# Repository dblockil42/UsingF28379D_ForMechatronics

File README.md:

<div id="top"></div>
<!--
*** Thanks for checking out the Best-README-Template. If you have a suggestion
*** that would make this better, please fork the repo and create a pull request
*** or simply open an issue with the tag "enhancement".
*** Don't forget to give the project a star!
*** Thanks again! Now go create something AMAZING! :D
-->

<!-- PROJECT SHIELDS -->
<!--
*** I'm using markdown "reference style" links for readability.
*** Reference links are enclosed in brackets [ ] instead of parentheses ( ).
*** See the bottom of this document for the declaration of the reference variables
*** for contributors-url, forks-url, etc. This is an optional, concise syntax you may use.
*** https://www.markdownguide.org/basic-syntax/#reference-style-links
-->
[![Contributors][contributors-shield]][contributors-url]
[![Forks][forks-shield]][forks-url]
[![Stargazers][stars-shield]][stars-url]
[![Issues][issues-shield]][issues-url]
[![MIT License][license-shield]][license-url]
[![LinkedIn][linkedin-shield]][linkedin-url]

<!-- PROJECT LOGO -->
<br />
<div align="center">

  <h3 align="center">Instructing Mechatronics with the Texas Instruments TMS320F28379D</h3>

  <p align="center">
    Mechatronics, Robotics and Real-Time Control with the TI TMS320F28379D Processor
    <br />
    <a href="https://github.com/dblockil42/UsingF28379D_ForMechatronics"><strong>Explore the docs »</strong></a>
    <br />
    <br />
    <a href="https://www.youtube.com/playlist?list=PL-l3usZMjrdI7pazXXURZ83wFKBJd2WC6">View YouTube Channel</a>
    ·
    <a href="https://github.com/dblockil42/UsingF28379D_ForMechatronics/issues">Report Bug</a>
    ·
    <a href="https://github.com/dblockil42/UsingF28379D_ForMechatronics/issues">Request Feature</a>
  </p>
</div>

<!-- TABLE OF CONTENTS -->
<details>
  <summary>Table of Contents</summary>
  <ol>
    <li>
      <a href="#about-the-project">About The Project</a>
      <ul>
        <li><a href="#built-with">Built With</a></li>
      </ul>
    </li>
    <li>
      <a href="#getting-started">Getting Started</a>
      <ul>
        <li><a href="#prerequisites">Prerequisites</a></li>
        <li><a href="#installation">Installation</a></li>
      </ul>
    </li>
    <li><a href="#usage">Usage</a></li>
    <li><a href="#roadmap">Roadmap</a></li>
    <li><a href="#contributing">Contributing</a></li>
    <li><a href="#license">License</a></li>
    <li><a href="#contact">Contact</a></li>
    <li><a href="#acknowledgments">Acknowledgments</a></li>
  </ol>
</details>

<!-- ABOUT THE PROJECT -->
## About The Project
The TMS320F28379D is an incredibly powerful processor for embedded control design.

I have been teaching with the C2000 series of processors since the early 2000s with the F2407 processor and a bit later the F2808.  Currently in my lab instruction I use the F28335, F28379D and F28027 processors.

I use the F2837x processor in the classes:
- [ME461, Computer Control of Mechanical Systems](http://coecsl.ece.illinois.edu/me461),
- [SE420, Digital Control of Dynamic Systems](http://coecsl.ece.illinois.edu/se420),
- [SE423, Mechatronics](http://coecsl.ece.illinois.edu/se423).  
	
You can find these classes and all the rest of the classes that use the Grainger College of Engineering Control Systems Lab at http://coecsl.ece.illinois.edu  

I have created a YouTube channel that has parts of my SE423 and ME461 lectures describing how to use/program the TMS320F28379D processor.  Please visit [Dan Block's YouTube Channel](https://www.youtube.com/watch?v=pqUko_UUdbc&list=PL-l3usZMjrdI7pazXXURZ83wFKBJd2WC6&index=1)
	
This is a picture and link to a final project that one of the students taking ME461 created. 
[![Product Name Screen Shot][product-screenshot]](https://www.hackster.io/yixiaol2/control-segbot-with-tv-remote-98b02c)
See her additional F28379D based projects at https://www.hackster.io/yixiaol2

<p align="right">(<a href="#top">back to top</a>)</p>

### Built With

Texas Instruments C2000Ware was used to develop the given C2000 projects.  If you are interested in the SYS/BIOS (coming soon) project you will need to also install SYS/BIOS under Code Composer Studio.

* [C2000Ware 4.01](https://www.ti.com/tool/C2000WARE)
* [SYS/BIOS 6.83.00.18](https://software-dl.ti.com/dsps/dsps_public_sw/sdo_sb/targetcontent/bios/sysbios/)

<p align="right">(<a href="#top">back to top</a>)</p>

<!-- GETTING STARTED -->
## Getting Started

You will need to have installed Texas Instruments Code Composer Studio.  I am currently using version 11.2

### Prerequisites

Access to the LAUNCHXL-F28379D Development Board https://www.ti.com/tool/LAUNCHXL-F28379D.

Fabricate the Breakout board I developed for the LAUNCHXL-F28379D https://github.com/dblockil42/UsingF28379D_ForMechatronics/tree/main/EagleCAD_ME461Board.

Knowledge of C programming is very important.

### Installation

_Steps for installing:_

1. Download and install CCS 11.2  [https://www.ti.com/tool/download/CCSTUDIO](https://www.ti.com/tool/download/CCSTUDIO)
2. Download and install C2000Ware 4.01 https://www.ti.com/tool/C2000WARE  Actually not directly needed, as all source code is included in this repository, but by installing C2000Ware you will agree with Texas Instruments License for C2000Ware.  
3. Clone the repo
   ```sh
   git clone https://github.com/dblockil42/UsingF28379D_ForMechatronics.git
   ```
4. Install SYS/BIOS if you would like to use the SYS/BIOS example (coming soon)

<p align="right">(<a href="#top">back to top</a>)</p>

<!-- USAGE EXAMPLES -->
## Usage

Best to start at the YouTube channel :  Coming Soon

For more examples, please refer to the class websites [SE423 (Mechatronics](http://coecsl.ece.illinois.edu/se423) and [ME461 (Computer Control of Mechanical Systems)](http://coecsl.ece.illinois.edu/me461)

<p align="right">(<a href="#top">back to top</a>)</p>

<!-- ROADMAP -->
## Roadmap

- [ ] Add More Starter Projects for additional Peripherals
- [ ] Add SYS/BIOS Starter Project
- [ ] Continue to add videos to YouTube channel explaining the given Starter Projects in detail.

See the [open issues](https://github.com/dblockil42/UsingF28379D_ForMechatronics/issues) for a full list of proposed features (and known issues).

<p align="right">(<a href="#top">back to top</a>)</p>

<!-- CONTRIBUTING -->
## Contributing

Contributions are what make the open source community such an amazing place to learn, inspire, and create. Any contributions you make are **greatly appreciated**.

If you have a suggestion that would make this better, please fork the repo and create a pull request. You can also simply open an issue with the tag "enhancement".
Don't forget to give the project a star! Thanks again!  Please Note, that during the two college semesters I am very busy instructing my classes so I cannot promise how quick I will get to new Pull Requests.  I will do my best to get to them.  

1. Fork the Project
2. Create your Feature Branch (`git checkout -b feature/AmazingFeature`)
3. Commit your Changes (`git commit -m 'Add some AmazingFeature'`)
4. Push to the Branch (`git push origin feature/AmazingFeature`)
5. Open a Pull Request

<p align="right">(<a href="#top">back to top</a>)</p>

<!-- LICENSE -->
## License

Distributed under the  MIT License. See `LICENSE.txt` for more information.

<p align="right">(<a href="#top">back to top</a>)</p>

<!-- CONTACT -->
## Contact

Dan Block -  dblockil42@gmail.com

Project Link: [https://github.com/dblockil42/UsingF28379D_ForMechatronics](https://github.com/dblockil42/UsingF28379D_ForMechatronics)

<p align="right">(<a href="#top">back to top</a>)</p>

<!-- ACKNOWLEDGMENTS -->
## Acknowledgments

Many of my students with their questions helped me put this together!  

* [Template this Readme Started From](https://github.com/othneildrew/Best-README-Template#top)
* [Choose an Open Source License](https://choosealicense.com)
* [GitHub Emoji Cheat Sheet](https://www.webpagefx.com/tools/emoji-cheat-sheet)
* [Malven's Flexbox Cheatsheet](https://flexbox.malven.co/)
* [Malven's Grid Cheatsheet](https://grid.malven.co/)
* [Img Shields](https://shields.io)
* [GitHub Pages](https://pages.github.com)
* [Font Awesome](https://fontawesome.com)
* [React Icons](https://react-icons.github.io/react-icons/search)

<p align="right">(<a href="#top">back to top</a>)</p>

<!-- MARKDOWN LINKS & IMAGES -->
<!-- https://www.markdownguide.org/basic-syntax/#reference-style-links -->
[contributors-shield]: https://img.shields.io/github/contributors/dblockil42/UsingF28379D_ForMechatronics.svg?style=for-the-badge
[contributors-url]: https://github.com/dblockil42/UsingF28379D_ForMechatronics/graphs/contributors
[forks-shield]: https://img.shields.io/github/forks/dblockil42/UsingF28379D_ForMechatronics.svg?style=for-the-badge
[forks-url]: https://github.com/dblockil42/UsingF28379D_ForMechatronics/network/members
[stars-shield]: https://img.shields.io/github/stars/dblockil42/UsingF28379D_ForMechatronics.svg?style=for-the-badge
[stars-url]: https://github.com/dblockil42/UsingF28379D_ForMechatronics/stargazers
[issues-shield]: https://img.shields.io/github/issues/dblockil42/UsingF28379D_ForMechatronics.svg?style=for-the-badge
[issues-url]: https://github.com/dblockil42/UsingF28379D_ForMechatronics/issues
[license-shield]: https://img.shields.io/github/license/dblockil42/UsingF28379D_ForMechatronics.svg?style=for-the-badge
[license-url]: https://github.com/dblockil42/UsingF28379D_ForMechatronics/blob/master/LICENSE.txt
[linkedin-shield]: https://img.shields.io/badge/-LinkedIn-black.svg?style=for-the-badge&logo=linkedin&colorB=555
[linkedin-url]: https://www.linkedin.com/in/dan-block-122b0315/
[product-screenshot]: Segbot.png

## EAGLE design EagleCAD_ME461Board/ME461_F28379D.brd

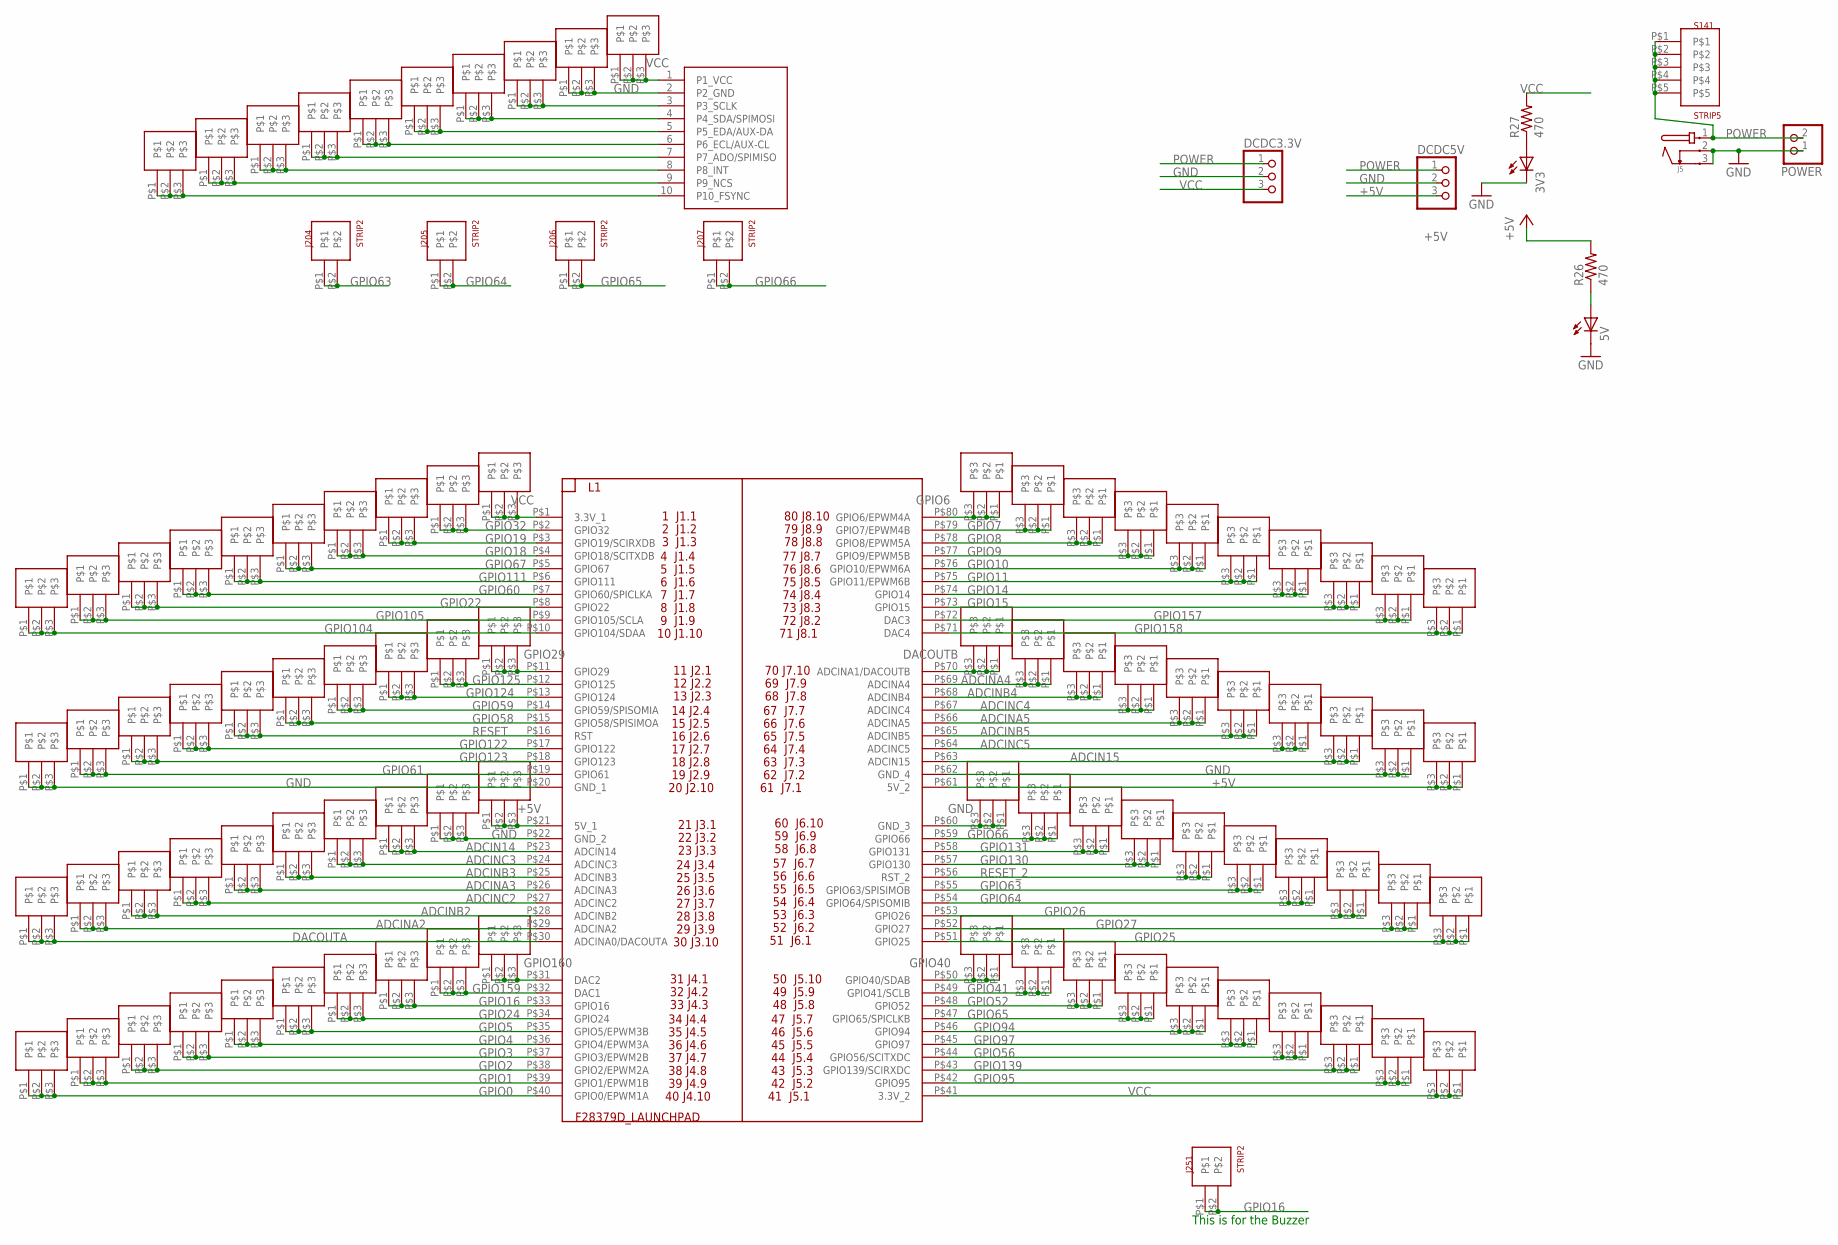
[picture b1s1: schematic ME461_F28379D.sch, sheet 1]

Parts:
3V3, 5V: LEDCHIPLED_1206; CHIPLED_1206
DCDC3.3V, DCDC5V: PINHD-1X3; 1X03
J5: JACK-PMS
J10, J14, J15, J16, J17, J18, J19, J20, J21, J28, J29, J30, J31, J32, J33, J98, J99, J100, J101, J102, J103, J104, J105, J106, J107, J108, J109, J110, J111, J112, J113, J114, J115, J116, J117, J118, J119, J120, J121, J122, J123, J124, J125, J126, J127, J128, J129, J130, J131, J132, J133, J134, J135, J136, J137, J138, J139, J140, J141, J142, J143, J144, J145, J146, J147, J148, J149, J150, J151, J152, J153, J154, J155, J156, J157, J158, J159, J160, J161, J162, J163, J164, J165, J166, J167, J168, J169, J170, J176, J177: STRIP3
J204, J205, J206, J207, J251: STRIP2
L1: F28379D_LAUNCHPAD
POWER: PINHD-1X2; 1X02
R26, R27: 470; M1206
S141: STRIP5
U$1: MPU-9250-BB

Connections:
+5V: DCDC5V.3, J103.P$1, J103.P$2, J103.P$3, J152.P$1, J152.P$2, J152.P$3, L1.P$21 (5V_1), L1.P$61 (5V_2), R26.2; also elsewhere on the board
ADCIN14: J105.P$1, J105.P$2, J105.P$3, L1.P$23 (ADCIN14)
ADCIN15: J150.P$1, J150.P$2, J150.P$3, L1.P$63 (ADCIN15)
ADCINA2: J111.P$1, J111.P$2, J111.P$3, L1.P$29 (ADCINA2); also elsewhere on the board
ADCINA3: J108.P$1, J108.P$2, J108.P$3, L1.P$26 (ADCINA3); also elsewhere on the board
ADCINA4: J144.P$1, J144.P$2, J144.P$3, L1.P$69 (ADCINA4)
ADCINA5: J147.P$1, J147.P$2, J147.P$3, L1.P$66 (ADCINA5)
ADCINB2: J110.P$1, J110.P$2, J110.P$3, L1.P$28 (ADCINB2)
ADCINB3: J107.P$1, J107.P$2, J107.P$3, L1.P$25 (ADCINB3)
ADCINB4: J145.P$1, J145.P$2, J145.P$3, L1.P$68 (ADCINB4); also elsewhere on the board
ADCINB5: J148.P$1, J148.P$2, J148.P$3, L1.P$65 (ADCINB5)
ADCINC2: J109.P$1, J109.P$2, J109.P$3, L1.P$27 (ADCINC2)
ADCINC3: J106.P$1, J106.P$2, J106.P$3, L1.P$24 (ADCINC3)
ADCINC4: J146.P$1, J146.P$2, J146.P$3, L1.P$67 (ADCINC4)
ADCINC5: J149.P$1, J149.P$2, J149.P$3, L1.P$64 (ADCINC5)
DACOUTA: J112.P$1, J112.P$2, J112.P$3, L1.P$30 (ADCINA0/DACOUTA)
DACOUTB: J143.P$1, J143.P$2, J143.P$3, L1.P$70 (ADCINA1/DACOUTB)
GND: 3V3.C, 5V.C, DCDC3.3V.2, DCDC5V.2, J5.2, J5.3, J102.P$1, J102.P$2, J102.P$3, J104.P$1, J104.P$2, J104.P$3, J124.P$1, J124.P$2, J124.P$3, J151.P$1, J151.P$2, J151.P$3, J153.P$1, J153.P$2, J153.P$3, L1.P$20 (GND_1), L1.P$22 (GND_2), L1.P$60 (GND_3), L1.P$62 (GND_4), POWER.1, U$1.2 (P2_GND); also elsewhere on the board
GPIO0: J122.P$1, J122.P$2, J122.P$3, L1.P$40 (GPIO0/EPWM1A); also elsewhere on the board
GPIO1: J121.P$1, J121.P$2, J121.P$3, L1.P$39 (GPIO1/EPWM1B); also elsewhere on the board
GPIO2: J120.P$1, J120.P$2, J120.P$3, L1.P$38 (GPIO2/EPWM2A); also elsewhere on the board
GPIO3: J119.P$1, J119.P$2, J119.P$3, L1.P$37 (GPIO3/EPWM2B); also elsewhere on the board
GPIO4: J118.P$1, J118.P$2, J118.P$3, L1.P$36 (GPIO4/EPWM3A); also elsewhere on the board
GPIO5: J117.P$1, J117.P$2, J117.P$3, L1.P$35 (GPIO5/EPWM3B); also elsewhere on the board
GPIO6: J133.P$1, J133.P$2, J133.P$3, L1.P$80 (GPIO6/EPWM4A); also elsewhere on the board
GPIO7: J134.P$1, J134.P$2, J134.P$3, L1.P$79 (GPIO7/EPWM4B); also elsewhere on the board
GPIO8: J135.P$1, J135.P$2, J135.P$3, L1.P$78 (GPIO8/EPWM5A); also elsewhere on the board
GPIO9: J136.P$1, J136.P$2, J136.P$3, L1.P$77 (GPIO9/EPWM5B); also elsewhere on the board
GPIO10: J137.P$1, J137.P$2, J137.P$3, L1.P$76 (GPIO10/EPWM6A); also elsewhere on the board
GPIO11: J138.P$1, J138.P$2, J138.P$3, L1.P$75 (GPIO11/EPWM6B); also elsewhere on the board
GPIO14: J139.P$1, J139.P$2, J139.P$3, L1.P$74 (GPIO14); also elsewhere on the board
GPIO15: J140.P$1, J140.P$2, J140.P$3, L1.P$73 (GPIO15); also elsewhere on the board
GPIO16: J115.P$1, J115.P$2, J115.P$3, J251.P$1, J251.P$2, L1.P$33 (GPIO16)
GPIO18: J16.P$1, J16.P$2, J16.P$3, L1.P$4 (GPIO18/SCITXDB); also elsewhere on the board
GPIO19: J15.P$1, J15.P$2, J15.P$3, L1.P$3 (GPIO19/SCIRXDB); also elsewhere on the board
GPIO22: J20.P$1, J20.P$2, J20.P$3, L1.P$8 (GPIO22); also elsewhere on the board
GPIO24: J116.P$1, J116.P$2, J116.P$3, L1.P$34 (GPIO24); also elsewhere on the board
GPIO25: J162.P$1, J162.P$2, J162.P$3, L1.P$51 (GPIO25); also elsewhere on the board
GPIO26: J160.P$1, J160.P$2, J160.P$3, L1.P$53 (GPIO26); also elsewhere on the board
GPIO27: J161.P$1, J161.P$2, J161.P$3, L1.P$52 (GPIO27); also elsewhere on the board
GPIO29: J29.P$1, J29.P$2, J29.P$3, L1.P$11 (GPIO29); also elsewhere on the board
GPIO32: J14.P$1, J14.P$2, J14.P$3, L1.P$2 (GPIO32); also elsewhere on the board
GPIO40: J163.P$1, J163.P$2, J163.P$3, L1.P$50 (GPIO40/SDAB); also elsewhere on the board
GPIO41: J164.P$1, J164.P$2, J164.P$3, L1.P$49 (GPIO41/SCLB); also elsewhere on the board
GPIO52: J165.P$1, J165.P$2, J165.P$3, L1.P$48 (GPIO52)
GPIO56: J169.P$1, J169.P$2, J169.P$3, L1.P$44 (GPIO56/SCITXDC); also elsewhere on the board
GPIO58: J33.P$1, J33.P$2, J33.P$3, L1.P$15 (GPIO58/SPISIMOA); also elsewhere on the board
GPIO59: J32.P$1, J32.P$2, J32.P$3, L1.P$14 (GPIO59/SPISOMIA); also elsewhere on the board
GPIO60: J19.P$1, J19.P$2, J19.P$3, L1.P$7 (GPIO60/SPICLKA); also elsewhere on the board
GPIO61: J101.P$1, J101.P$2, J101.P$3, L1.P$19 (GPIO61); also elsewhere on the board
GPIO63: J158.P$1, J158.P$2, J158.P$3, J204.P$1, J204.P$2, L1.P$55 (GPIO63/SPISIMOB); also elsewhere on the board
GPIO64: J159.P$1, J159.P$2, J159.P$3, J205.P$1, J205.P$2, L1.P$54 (GPIO64/SPISOMIB); also elsewhere on the board
GPIO65: J166.P$1, J166.P$2, J166.P$3, J206.P$1, J206.P$2, L1.P$47 (GPIO65/SPICLKB); also elsewhere on the board
GPIO66: J154.P$1, J154.P$2, J154.P$3, J207.P$1, J207.P$2, L1.P$59 (GPIO66)
GPIO67: J17.P$1, J17.P$2, J17.P$3, L1.P$5 (GPIO67)
GPIO94: J167.P$1, J167.P$2, J167.P$3, L1.P$46 (GPIO94); also elsewhere on the board
GPIO95: J176.P$1, J176.P$2, J176.P$3, L1.P$42 (GPIO95); also elsewhere on the board
GPIO97: J168.P$1, J168.P$2, J168.P$3, L1.P$45 (GPIO97); also elsewhere on the board
GPIO104: J28.P$1, J28.P$2, J28.P$3, L1.P$10 (GPIO104/SDAA)
GPIO105: J21.P$1, J21.P$2, J21.P$3, L1.P$9 (GPIO105/SCLA)
GPIO111: J18.P$1, J18.P$2, J18.P$3, L1.P$6 (GPIO111); also elsewhere on the board
GPIO122: J99.P$1, J99.P$2, J99.P$3, L1.P$17 (GPIO122); also elsewhere on the board
GPIO123: J100.P$1, J100.P$2, J100.P$3, L1.P$18 (GPIO123); also elsewhere on the board
GPIO124: J31.P$1, J31.P$2, J31.P$3, L1.P$13 (GPIO124); also elsewhere on the board
GPIO125: J30.P$1, J30.P$2, J30.P$3, L1.P$12 (GPIO125); also elsewhere on the board
GPIO130: J156.P$1, J156.P$2, J156.P$3, L1.P$57 (GPIO130); also elsewhere on the board
GPIO131: J155.P$1, J155.P$2, J155.P$3, L1.P$58 (GPIO131); also elsewhere on the board
GPIO139: J170.P$1, J170.P$2, J170.P$3, L1.P$43 (GPIO139/SCIRXDC); also elsewhere on the board
GPIO157: J141.P$1, J141.P$2, J141.P$3, L1.P$72 (DAC3); also elsewhere on the board
GPIO158: J142.P$1, J142.P$2, J142.P$3, L1.P$71 (DAC4); also elsewhere on the board
GPIO159: J114.P$1, J114.P$2, J114.P$3, L1.P$32 (DAC1); also elsewhere on the board
GPIO160: J113.P$1, J113.P$2, J113.P$3, L1.P$31 (DAC2); also elsewhere on the board
unnamed: 3V3.A, R27.1
unnamed: 5V.A, R26.1
unnamed: J125.P$1, J125.P$2, J125.P$3, U$1.3 (P3_SCLK)
unnamed: J126.P$1, J126.P$2, J126.P$3, U$1.4 (P4_SDA/SPIMOSI)
unnamed: J127.P$1, J127.P$2, J127.P$3, U$1.5 (P5_EDA/AUX-DA)
unnamed: J128.P$1, J128.P$2, J128.P$3, U$1.6 (P6_ECL/AUX-CL)
unnamed: J129.P$1, J129.P$2, J129.P$3, U$1.7 (P7_ADO/SPIMISO)
unnamed: J130.P$1, J130.P$2, J130.P$3, U$1.8 (P8_INT)
unnamed: J131.P$1, J131.P$2, J131.P$3, U$1.9 (P9_NCS)
unnamed: J132.P$1, J132.P$2, J132.P$3, U$1.10 (P10_FSYNC)
POWER: DCDC3.3V.1, DCDC5V.1, J5.1, POWER.2, S141.P$1, S141.P$2, S141.P$3, S141.P$4, S141.P$5; also elsewhere on the board
RESET: J98.P$1, J98.P$2, J98.P$3, L1.P$16 (RST)
RESET_2: J157.P$1, J157.P$2, J157.P$3, L1.P$56 (RST_2)
VCC: DCDC3.3V.3, J10.P$1, J10.P$2, J10.P$3, J123.P$1, J123.P$2, J123.P$3, J177.P$1, J177.P$2, J177.P$3, L1.P$1 (3.3V_1), L1.P$41 (3.3V_2), R27.2, U$1.1 (P1_VCC); also elsewhere on the board

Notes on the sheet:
This is for the Buzzer

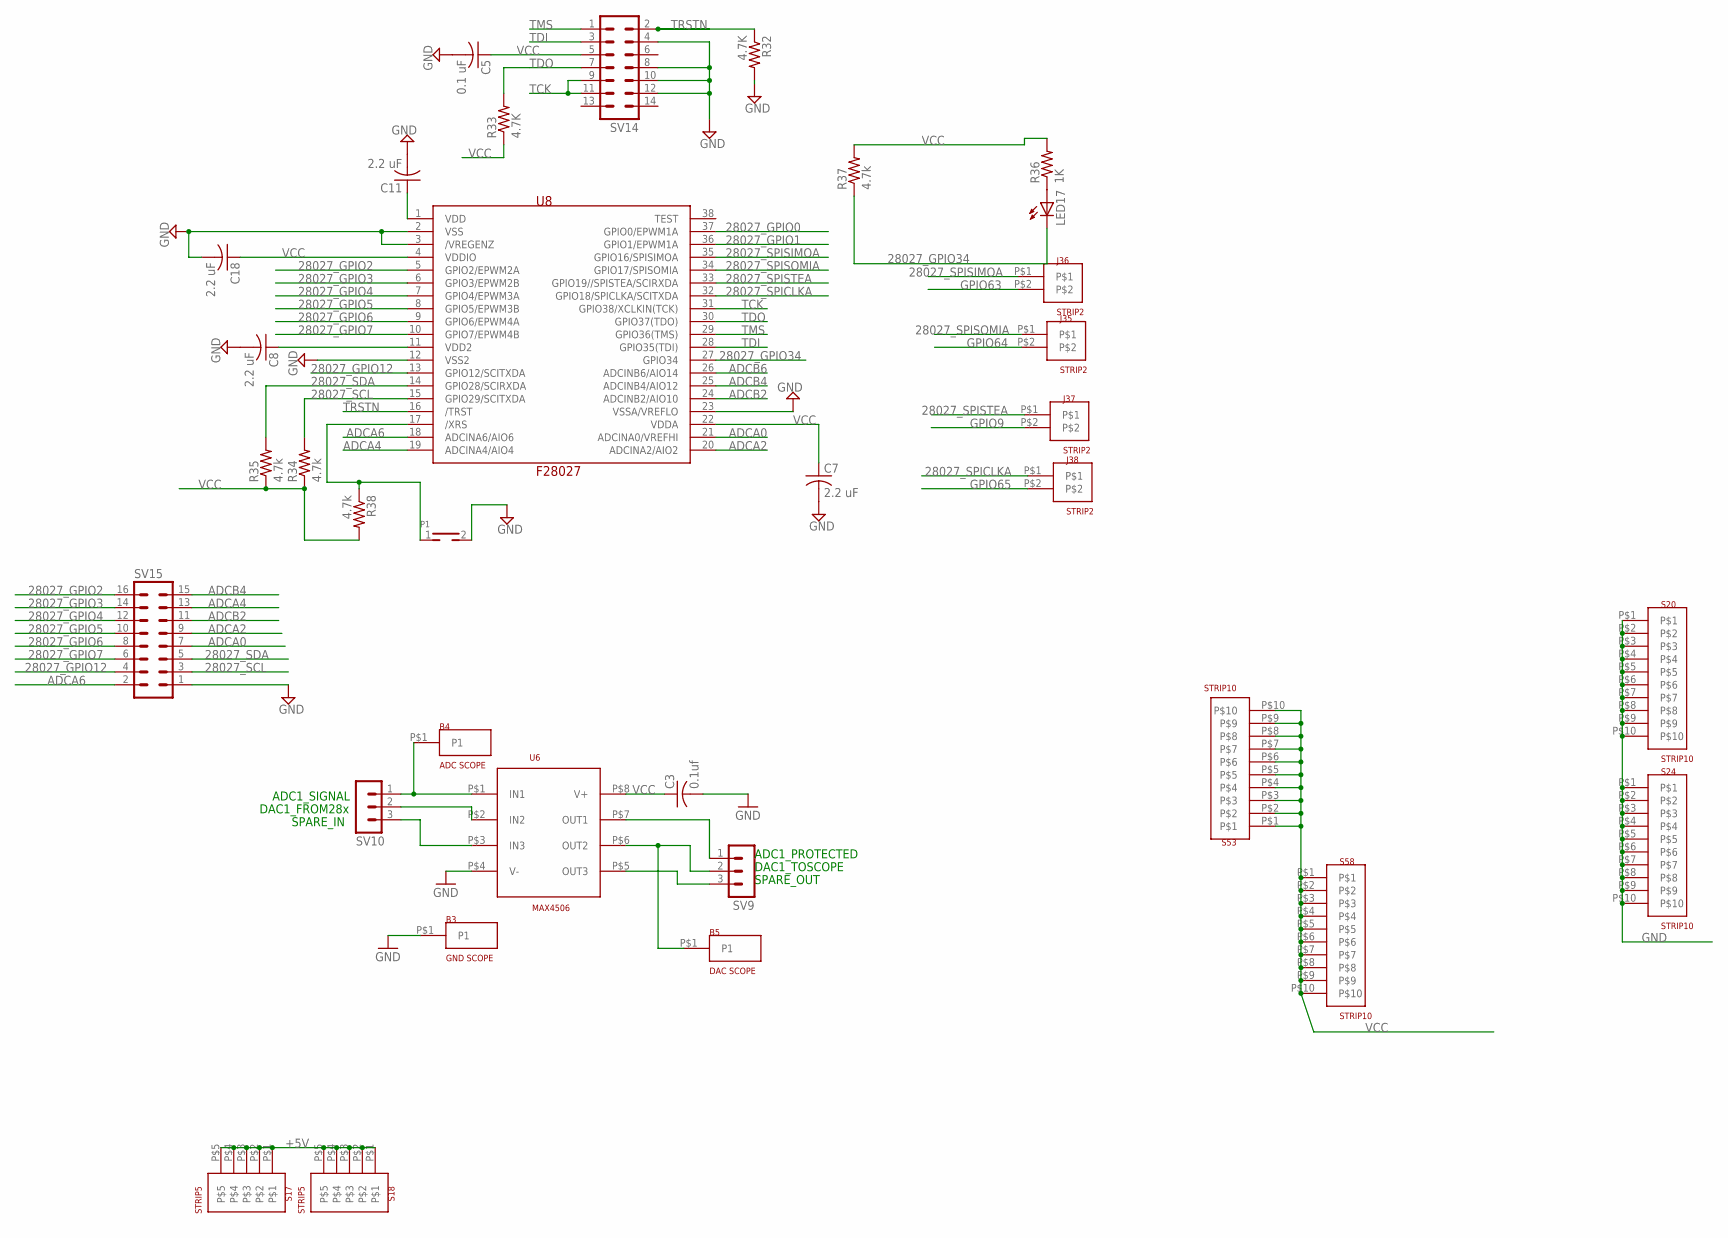
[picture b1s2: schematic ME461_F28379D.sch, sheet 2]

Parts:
B3: GND SCOPE; BANANA_MALE
B4: ADC SCOPE; BANANA_MALE
B5: DAC SCOPE; BANANA_MALE
C3: 0.1uf; C1206
C5: 0.1 uF; C1206
C7, C8, C11, C18: 2.2 uF; C1206
J35, J36, J37, J38: STRIP2
LED17: LEDCHIPLED_1206; CHIPLED_1206
P1: TH_PUSHBOTTON; TH_PUSHBUTTON
R32, R33: 4.7K; M1206
R34, R35, R37, R38: 4.7k; M1206
R36: 1K; M1206
S17, S18: STRIP5
S20, S24, S53, S58: STRIP10
SV9, SV10: MA03-1
SV14: MA07-2
SV15: MA08-2
U6: MAX4506; SOIC-8
U8: F28027; DA38

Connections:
28027_GPIO0: U8.37 (GPIO0/EPWM1A); also elsewhere on the board
28027_GPIO1: U8.36 (GPIO1/EPWM1A); also elsewhere on the board
28027_GPIO2: SV15.16, U8.5 (GPIO2/EPWM2A)
28027_GPIO3: SV15.14, U8.6 (GPIO3/EPWM2B)
28027_GPIO4: SV15.12, U8.7 (GPIO4/EPWM3A)
28027_GPIO5: SV15.10, U8.8 (GPIO5/EPWM3B)
28027_GPIO6: SV15.8, U8.9 (GPIO6/EPWM4A)
28027_GPIO7: SV15.6, U8.10 (GPIO7/EPWM4B)
28027_GPIO12: SV15.4, U8.13 (GPIO12/SCITXDA)
28027_GPIO34: LED17.C, R37.1, U8.27 (GPIO34)
28027_SCL: R34.2, SV15.3, U8.15 (GPIO29/SCITXDA)
28027_SDA: R35.2, SV15.5, U8.14 (GPIO28/SCIRXDA)
28027_SPICLKA: J38.P$1, U8.32 (GPIO18/SPICLKA/SCITXDA)
28027_SPISIMOA: J36.P$1, U8.35 (GPIO16/SPISIMOA)
28027_SPISOMIA: J35.P$1, U8.34 (GPIO17/SPISOMIA)
28027_SPISTEA: J37.P$1, U8.33 (GPIO19//SPISTEA/SCIRXDA)
+5V: S17.P$1, S17.P$2, S17.P$3, S17.P$4, S17.P$5, S18.P$1, S18.P$2, S18.P$3, S18.P$4, S18.P$5; also elsewhere on the board
ADCA0: SV15.7, U8.21 (ADCINA0/VREFHI)
ADCA2: SV15.9, U8.20 (ADCINA2/AIO2)
ADCA4: SV15.13, U8.19 (ADCINA4/AIO4)
ADCA6: SV15.2, U8.18 (ADCINA6/AIO6)
ADCB2: SV15.11, U8.24 (ADCINB2/AIO10)
ADCB4: SV15.15, U8.25 (ADCINB4/AIO12)
ADCB6: U8.26 (ADCINB6/AIO14)
GND: B3.P$1, C3.2, C5.2, C7.2, C8.2, C11.2, C18.2, P1.2, R32.2, S20.P$1, S20.P$2, S20.P$3, S20.P$4, S20.P$5, S20.P$6, S20.P$7, S20.P$8, S20.P$9, S20.P$10, S24.P$1, S24.P$2, S24.P$3, S24.P$4, S24.P$5, S24.P$6, S24.P$7, S24.P$8, S24.P$9, S24.P$10, SV14.4, SV14.8, SV14.10, SV14.12, SV15.1, U6.P$4 (V-), U8.2 (VSS), U8.3 (/VREGENZ), U8.12 (VSS2), U8.23 (VSSA/VREFLO); also elsewhere on the board
GPIO9: J37.P$2; also elsewhere on the board
GPIO63: J36.P$2; also elsewhere on the board
GPIO64: J35.P$2; also elsewhere on the board
GPIO65: J38.P$2; also elsewhere on the board
unnamed: SV9.1, U6.P$7 (OUT1)
unnamed: B5.P$1, SV9.2, U6.P$6 (OUT2)
unnamed: SV9.3, U6.P$5 (OUT3)
unnamed: B4.P$1, SV10.1, U6.P$1 (IN1)
unnamed: SV10.2, U6.P$2 (IN2)
unnamed: SV10.3, U6.P$3 (IN3)
unnamed: C11.1, U8.1 (VDD)
unnamed: C8.1, U8.11 (VDD2)
unnamed: P1.1, R38.1, U8.17 (/XRS)
unnamed: LED17.A, R36.1
TCK: SV14.9, SV14.11, U8.31 (GPIO38/XCLKIN(TCK))
TDI: SV14.3, U8.28 (GPIO35(TDI))
TDO: R33.2, SV14.7, U8.30 (GPIO37(TDO))
TMS: SV14.1, U8.29 (GPIO36(TMS))
TRSTN: R32.1, SV14.2, U8.16 (/TRST)
VCC: C3.1, C5.1, C7.1, C18.1, R33.1, R34.1, R35.1, R36.2, R37.2, R38.2, S53.P$1, S53.P$2, S53.P$3, S53.P$4, S53.P$5, S53.P$6, S53.P$7, S53.P$8, S53.P$9, S53.P$10, S58.P$1, S58.P$2, S58.P$3, S58.P$4, S58.P$5, S58.P$6, S58.P$7, S58.P$8, S58.P$9, S58.P$10, SV14.5, U6.P$8 (V+), U8.4 (VDDIO), U8.22 (VDDA); also elsewhere on the board

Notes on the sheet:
ADC1_SIGNAL
ADC1_PROTECTED
DAC1_FROM28x
DAC1_TOSCOPE
SPARE_IN
SPARE_OUT

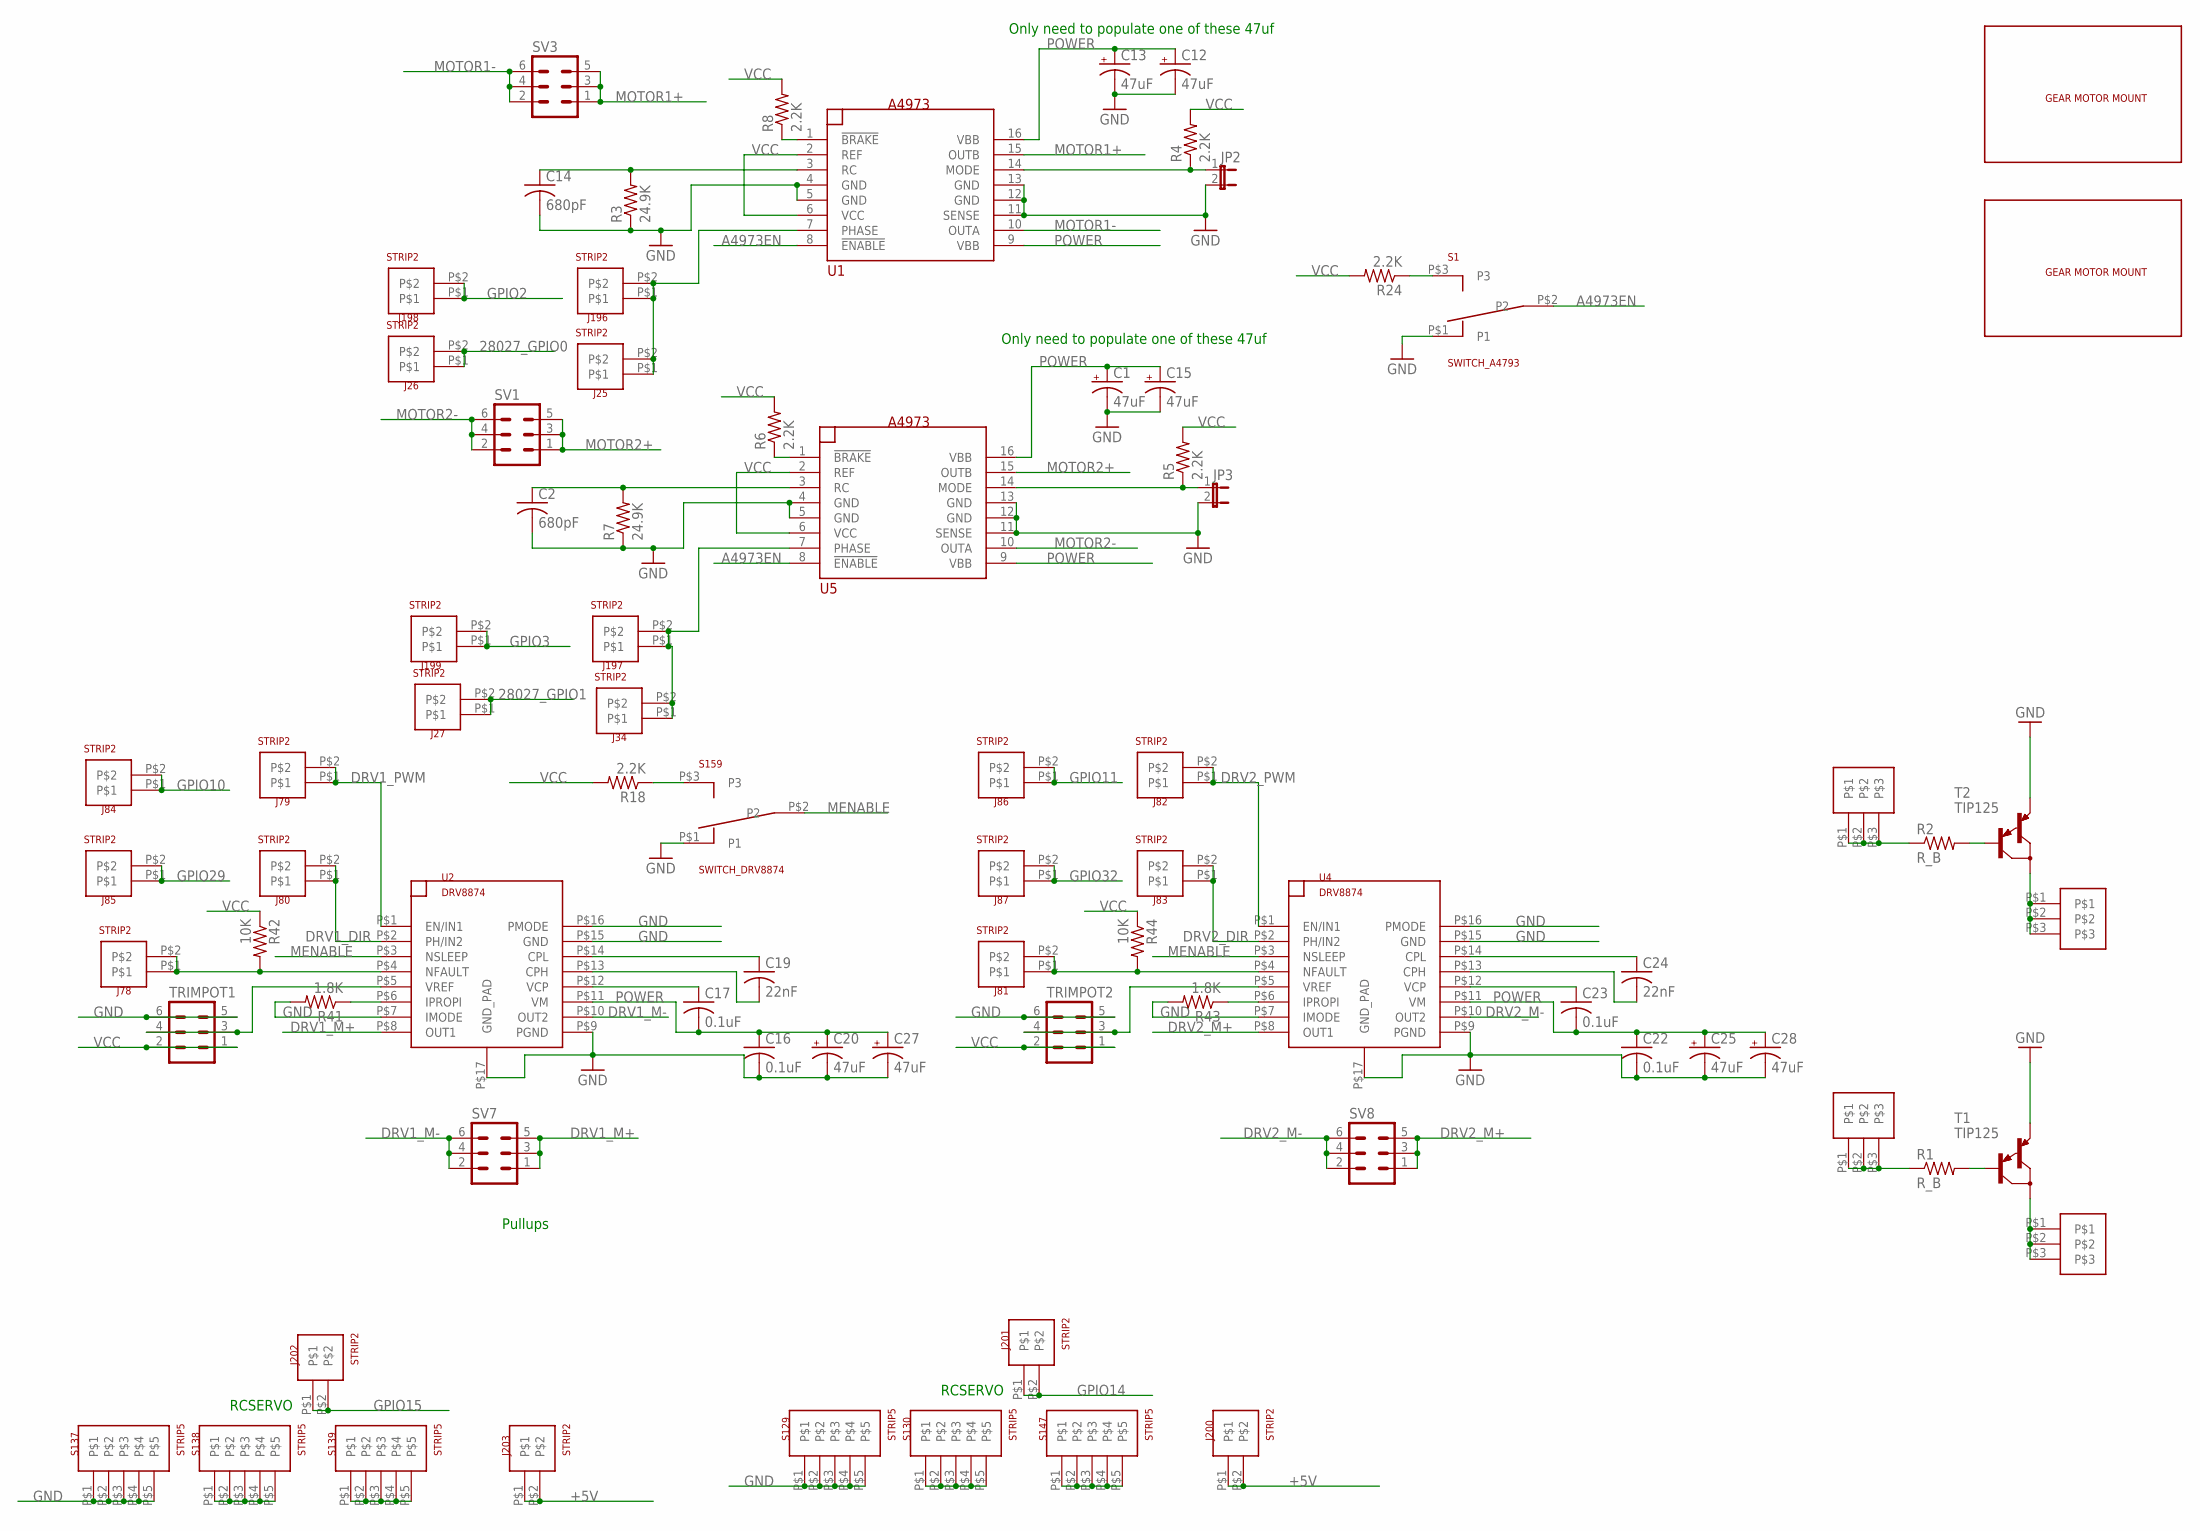
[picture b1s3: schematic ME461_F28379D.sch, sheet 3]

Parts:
C1, C12, C13, C15, C20, C25, C27, C28: 47uF; 153CLV-0810
C2, C14: 680pF; C1206
C16, C17, C22, C23: 0.1uF; C1206
C19, C24: 22nF; C1206
J4, J6, J23, J24: STRIP3
J25, J26, J27, J34, J78, J79, J80, J81, J82, J83, J84, J85, J86, J87, J196, J197, J198, J199, J200, J201, J202, J203: STRIP2
JP2, JP3: JP1E; JP1
R1, R2: R_B; 0207/10
R3, R7: 24.9K; M1206
R4, R5, R6, R8, R18, R24: 2.2K; M1206
R41, R43: 1.8K; M1206
R42, R44: 10K; M1206
S1: SWITCH_A4793; SWITCH_SLIDE
S129, S130, S137, S138, S139, S147: STRIP5
S159: SWITCH_DRV8874; SWITCH_SLIDE
SV1, SV3, SV7, SV8: MA03-2
T1, T2: TIP125; TO220
TRIMPOT1, TRIMPOT2: MA03-2
U1, U5: A4973; SO16W_LONGERPINS
U2, U4: DRV8874; HTSSOP16
U$2, U$3: GEARMOTOR_MOUNT

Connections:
28027_GPIO0: J26.P$1, J26.P$2; also elsewhere on the board
28027_GPIO1: J27.P$1, J27.P$2; also elsewhere on the board
+5V: J200.P$1, J200.P$2, J203.P$1, J203.P$2; also elsewhere on the board
A4973EN: S1.P$2 (P2), U1.8 (!ENABLE), U5.8 (!ENABLE)
DRV1_DIR: J80.P$1, J80.P$2, U2.P$2 (PH/IN2)
DRV1_M+: SV7.1, SV7.3, SV7.5, U2.P$8 (OUT1)
DRV1_M-: SV7.2, SV7.4, SV7.6, U2.P$10 (OUT2)
DRV1_PWM: J79.P$1, J79.P$2, U2.P$1 (EN/IN1)
DRV2_DIR: J83.P$1, J83.P$2, U4.P$2 (PH/IN2)
DRV2_M+: SV8.1, SV8.3, SV8.5, U4.P$8 (OUT1)
DRV2_M-: SV8.2, SV8.4, SV8.6, U4.P$10 (OUT2)
DRV2_PWM: J82.P$1, J82.P$2, U4.P$1 (EN/IN1)
GND: C1.-, C2.2, C12.-, C13.-, C14.2, C15.-, C16.2, C20.-, C22.2, C25.-, C27.-, C28.-, JP2.2, JP3.2, R3.1, R7.1, R41.2, R43.2, S1.P$1 (P1), S129.P$1, S129.P$2, S129.P$3, S129.P$4, S129.P$5, S137.P$1, S137.P$2, S137.P$3, S137.P$4, S137.P$5, S159.P$1 (P1), T1.3 (E), T2.3 (E), TRIMPOT1.5, TRIMPOT1.6, TRIMPOT2.5, TRIMPOT2.6, U1.4 (GND), U1.5 (GND), U1.11 (SENSE), U1.12 (GND), U1.13 (GND), U2.P$7 (IMODE), U2.P$9 (PGND), U2.P$15 (GND), U2.P$16 (PMODE), U2.P$17 (GND_PAD), U4.P$7 (IMODE), U4.P$9 (PGND), U4.P$15 (GND), U4.P$16 (PMODE), U4.P$17 (GND_PAD), U5.4 (GND), U5.5 (GND), U5.11 (SENSE), U5.12 (GND), U5.13 (GND); also elsewhere on the board
GPIO2: J198.P$1, J198.P$2; also elsewhere on the board
GPIO3: J199.P$1, J199.P$2; also elsewhere on the board
GPIO10: J84.P$1, J84.P$2; also elsewhere on the board
GPIO11: J86.P$1, J86.P$2; also elsewhere on the board
GPIO14: J201.P$1, J201.P$2; also elsewhere on the board
GPIO15: J202.P$1, J202.P$2; also elsewhere on the board
GPIO29: J85.P$1, J85.P$2; also elsewhere on the board
GPIO32: J87.P$1, J87.P$2; also elsewhere on the board
MENABLE: S159.P$2 (P2), U2.P$3 (NSLEEP), U4.P$3 (NSLEEP)
MOTOR1+: SV3.1, SV3.3, SV3.5, U1.15 (OUTB)
MOTOR1-: SV3.2, SV3.4, SV3.6, U1.10 (OUTA)
MOTOR2+: SV1.1, SV1.3, SV1.5, U5.15 (OUTB)
MOTOR2-: SV1.2, SV1.4, SV1.6, U5.10 (OUTA)
unnamed: R24.1, S1.P$3 (P3)
unnamed: S139.P$1, S139.P$2, S139.P$3, S139.P$4, S139.P$5
unnamed: S147.P$1, S147.P$2, S147.P$3, S147.P$4, S147.P$5
unnamed: R2.2, T2.1 (B)
unnamed: R1.2, T1.1 (B)
unnamed: S138.P$1, S138.P$2, S138.P$3, S138.P$4, S138.P$5
unnamed: R6.1, U5.1 (!BRAKE)
unnamed: C2.1, R7.2, U5.3 (RC)
unnamed: R8.1, U1.1 (!BRAKE)
unnamed: C14.1, R3.2, U1.3 (RC)
unnamed: JP2.1, R4.1, U1.14 (MODE)
unnamed: R18.1, S159.P$3 (P3)
unnamed: JP3.1, R5.1, U5.14 (MODE)
unnamed: C19.1, U2.P$14 (CPL)
unnamed: C19.2, U2.P$13 (CPH)
unnamed: C17.1, U2.P$12 (VCP)
unnamed: R43.1, U4.P$6 (IPROPI)
unnamed: R41.1, U2.P$6 (IPROPI)
unnamed: J78.P$1, J78.P$2, R42.2, U2.P$4 (NFAULT)
unnamed: TRIMPOT1.3, TRIMPOT1.4, U2.P$5 (VREF)
unnamed: C24.1, U4.P$14 (CPL)
unnamed: C24.2, U4.P$13 (CPH)
unnamed: C23.1, U4.P$12 (VCP)
unnamed: J81.P$1, J81.P$2, R44.2, U4.P$4 (NFAULT)
unnamed: TRIMPOT2.3, TRIMPOT2.4, U4.P$5 (VREF)
unnamed: S130.P$1, S130.P$2, S130.P$3, S130.P$4, S130.P$5
unnamed: J25.P$1, J25.P$2, J196.P$1, J196.P$2, U1.7 (PHASE)
unnamed: J34.P$1, J34.P$2, J197.P$1, J197.P$2, U5.7 (PHASE)
POWER: C1.+, C12.+, C13.+, C15.+, C16.1, C17.2, C20.+, C22.1, C23.2, C25.+, C27.+, C28.+, U1.9 (VBB), U1.16 (VBB), U2.P$11 (VM), U4.P$11 (VM), U5.9 (VBB), U5.16 (VBB); also elsewhere on the board
TR_BASE: J6.P$1, J6.P$2, J6.P$3, R1.1
TR_BASE1: J24.P$1, J24.P$2, J24.P$3, R2.1
TR_LOAD: J4.P$1, J4.P$2, J4.P$3, T1.2 (C)
TR_LOAD1: J23.P$1, J23.P$2, J23.P$3, T2.2 (C)
VCC: R4.2, R5.2, R6.2, R8.2, R18.2, R24.2, R42.1, R44.1, TRIMPOT1.1, TRIMPOT1.2, TRIMPOT2.1, TRIMPOT2.2, U1.2 (REF), U1.6 (VCC), U5.2 (REF), U5.6 (VCC); also elsewhere on the board

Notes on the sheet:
Pullups
RCSERVO
Only need to populate one of these 47uf
